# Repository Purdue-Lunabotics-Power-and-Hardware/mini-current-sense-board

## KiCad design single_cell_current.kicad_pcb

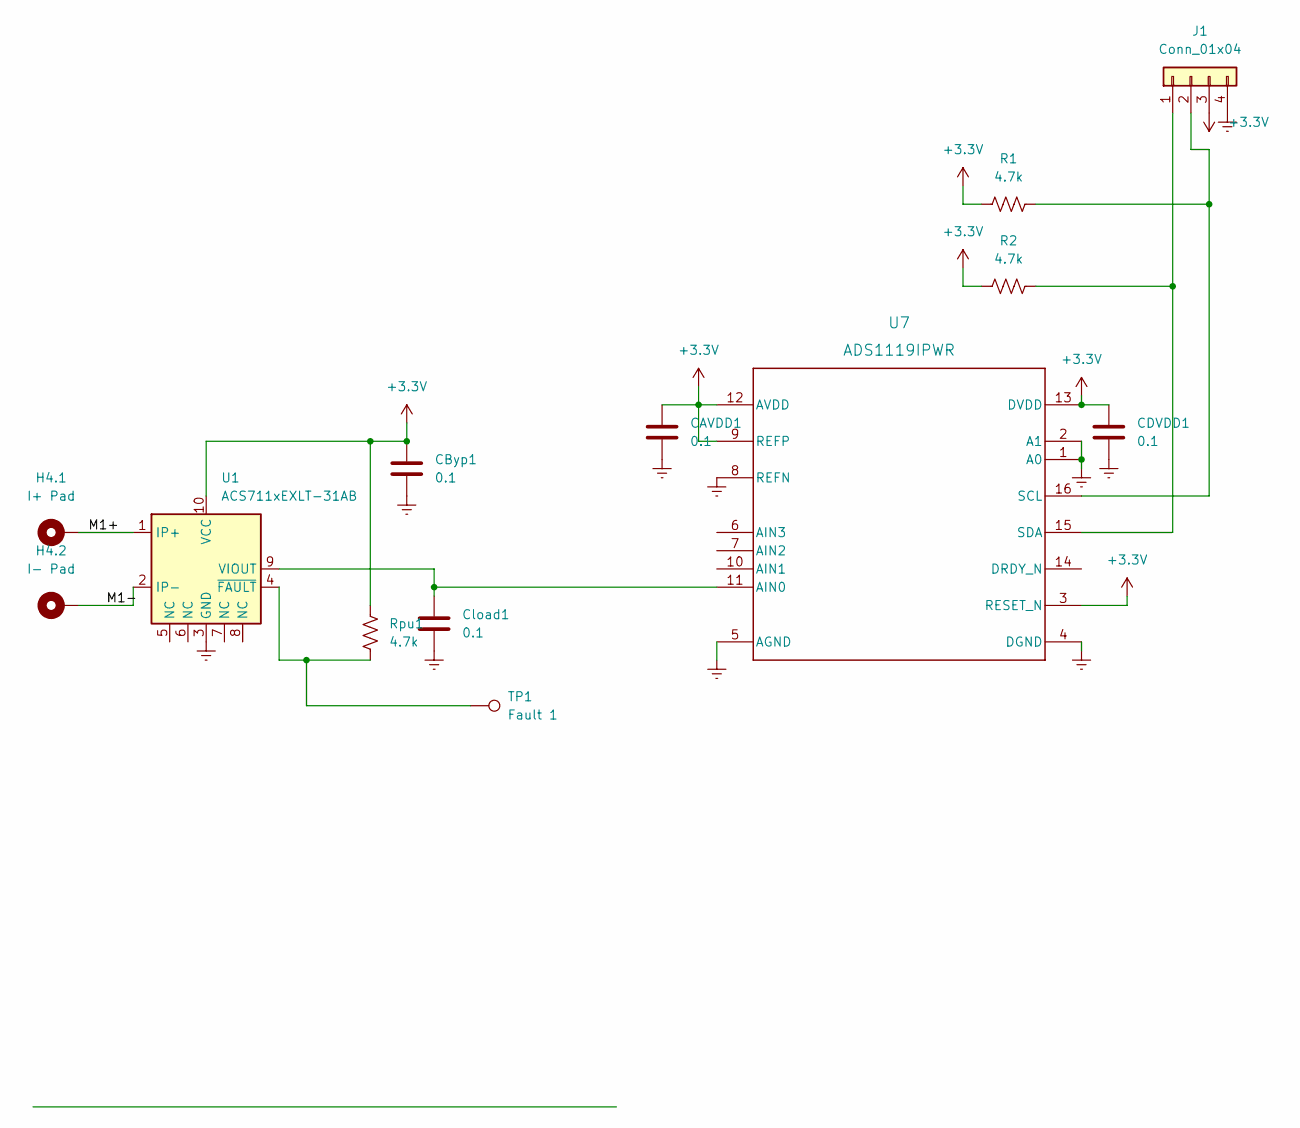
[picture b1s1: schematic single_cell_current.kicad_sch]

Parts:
CAVDD1: 0.1; C_0805_2012Metric_Pad1.18x1.45mm_HandSolder
CByp1: 0.1; C_0805_2012Metric_Pad1.18x1.45mm_HandSolder
CDVDD1: 0.1; C_0805_2012Metric_Pad1.18x1.45mm_HandSolder
Cload1: 0.1; C_0805_2012Metric_Pad1.18x1.45mm_HandSolder
H4.1: I+ Pad; SolderWire-0.25sqmm_1x01_D0.65mm_OD2mm
H4.2: I- Pad; SolderWire-0.25sqmm_1x01_D0.65mm_OD2mm
J1: Conn_01x04; JST_XH_S4B-XH-A_1x04_P2.50mm_Horizontal
R1, R2: 4.7k; R_0805_2012Metric_Pad1.20x1.40mm_HandSolder
Rpu1: 4.7k; R_0805_2012Metric_Pad1.20x1.40mm_HandSolder
TP1: Fault 1; SolderWire-0.1sqmm_1x01_D0.4mm_OD1mm
U1: ACS711xEXLT-31AB; Allegro_QFN-12-10-1EP_3x3mm_P0.5mm
U7: ADS1119IPWR; TSSOP-16_4.4x5mm_P0.65mm

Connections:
+3.3V: CAVDD1.1, CByp1.1, CDVDD1.1, J1.3, R1.1, R2.1, Rpu1.1, U1.10 (VCC), U7.3 (RESET_N), U7.9 (REFP), U7.12 (AVDD), U7.13 (DVDD)
/M1+: H4.1.1, U1.1 (IP+)
/M1-: H4.2.1, U1.2 (IP-)
Earth: CAVDD1.2, CByp1.2, CDVDD1.2, Cload1.2, J1.4, U1.3 (GND), U7.1 (A0), U7.2 (A1), U7.4 (DGND), U7.5 (AGND), U7.8 (REFN)
unnamed: J1.1, R2.2, U7.15 (SDA)
unnamed: J1.2, R1.2, U7.16 (SCL)
unnamed: Rpu1.2, TP1.1, U1.4 (~FAULT)
unnamed: Cload1.1, U1.9 (VIOUT), U7.11 (AIN0)

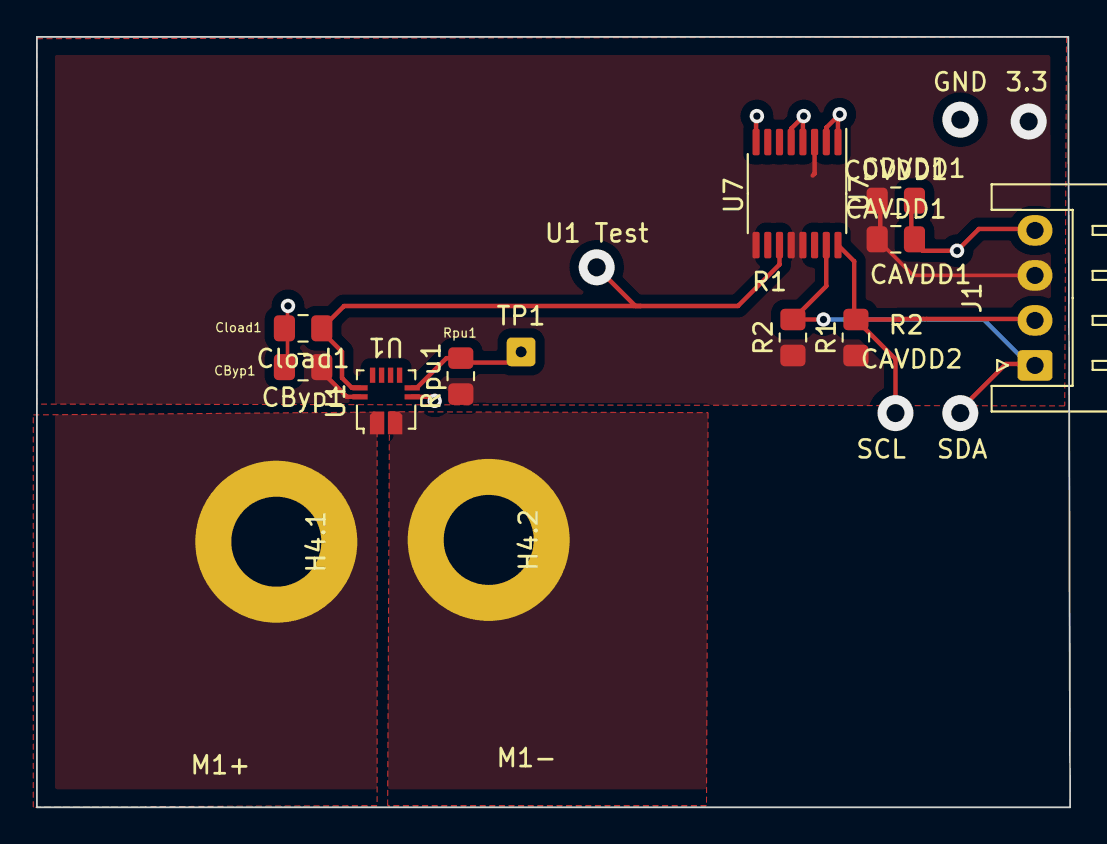
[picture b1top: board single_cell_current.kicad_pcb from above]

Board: 2 copper layers, 57.4 x 42.8 mm, 13 parts (0 on the bottom side), 8 nets.

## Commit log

2024-03-26 Initial upload with milled files
